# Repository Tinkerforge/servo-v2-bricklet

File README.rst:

Servo Bricklet 2.0
==================

This repository contains the firmware source code and the hardware design
files. The documentation generator configs can be found at
https://github.com/Tinkerforge/generators

Repository Content
------------------

software/:
 * examples/: Examples for all supported languages
 * build/: Compiled files
 * src/: Source code of firmware
 * Makefile: Makefile to build project

hardware/:
 * Contains KiCad project files and additionally schematics as PDF

datasheets/:
 * Contains datasheets for sensors and complex ICs that are used

Hardware
--------

The hardware is designed with the open source EDA Suite KiCad
(http://www.kicad.org). Before you are able to open the files,
you have to install the Tinkerforge kicad-libraries
(https://github.com/Tinkerforge/kicad-libraries). You can either clone
them directly in hardware/ or clone them in a separate folder and
symlink them into hardware/
(ln -s kicad_path/kicad-libraries project_path/hardware). After that you
can open the .pro file in hardware/ with KiCad and from there view and
modify the schematics and the PCB layout.

Software
--------

If you want to do your own Brick/Bricklet firmware development we highly
recommend that you use our build environment setup script and read the
tutorial (https://www.tinkerforge.com/en/doc/Tutorials/Tutorial_Build_Environment/Tutorial.html).

To compile the C code we recommend you to install the newest GNU Arm Embedded
Toolchain (https://launchpad.net/gcc-arm-embedded/+download).
You also need to install bricklib2 (https://github.com/Tinkerforge/bricklib2).

You can either clone it directly in software/src/ or clone it in a
separate folder and symlink it into software/src/
(ln -s bricklib_path/bricklib2 project_path/software/src/). Finally make sure to
have CMake installed (http://www.cmake.org/cmake/resources/software.html).

After that you can build the firmware by invoking make in software/.
The firmware (.zbin) can then be found in software/build/ and uploaded
with brickv (click button "Flashing" on start screen).

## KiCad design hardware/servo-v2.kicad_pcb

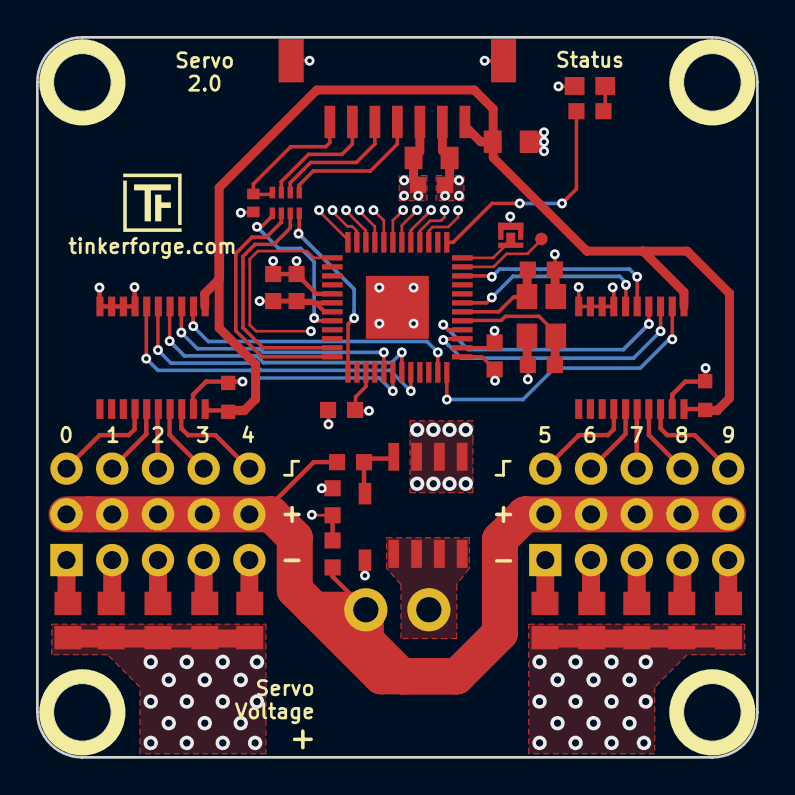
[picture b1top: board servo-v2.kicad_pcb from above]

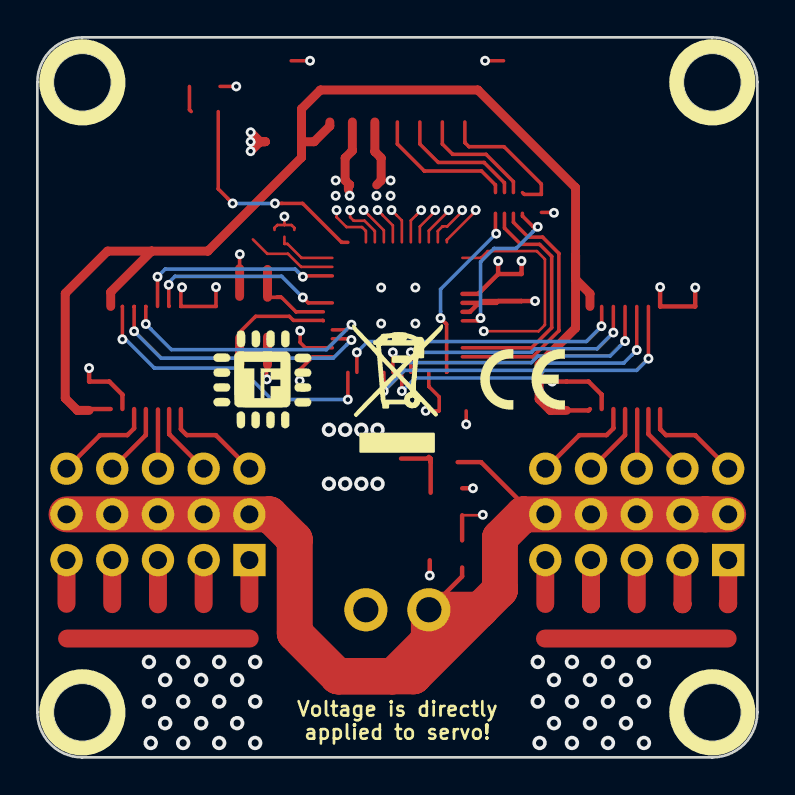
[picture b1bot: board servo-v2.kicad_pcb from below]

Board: 4 copper layers, 40.0 x 40.0 mm, 46 parts (2 on the bottom side), 51 nets.

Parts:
C1, C12: 10uF; C0805
C2: 1uF; C0603F
C3, C4, C5: 100nF; C0603F
C6: 220nF; C0603F
C7: 220pF; C0402F
C8, C9: 10pF; C0603F
C10, C11: 100nF; C0603
D1: Z12V; SOD-123
D3: blue; D0603E
P1: CON-SENSOR2
P2: BOOT; SolderJumper
P3: DEBUG; DEBUG_PAD
P4: black; OQ_2P
Q1: FDS8449; SOIC-8-MOSFET
R1, R3: 1k; R0603F
R2: 10k; R0603F
R4, R5, R6, R7, R8, R9, R10, R11, R12, R13: 0R1; R0805E
R16: 100k; R0603F
RP1: 82; 4X0402
U1: XMC1404; QFN48-EP2
U2, U3, U4, U5: DRILL; DRILL_NP
U6, U7: 74HC245; TSSOP20
U8, U9: Con_Servo_5x; pin_array_5x3
VAL: CE_5mm
VAL#2: WEEE_7mm
X1: 16MHz; CRYSTAL_3225

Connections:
+5V: C10.1, C11.2, C12.1, P1.1, U6.1, U6.20, U7.1, U7.20
CUR-SERVO-0: R8.1, U1.8, U8.A1
CUR-SERVO-1: R7.1, U1.9, U8.B1
CUR-SERVO-2: R6.1, U1.10, U8.C1
CUR-SERVO-3: R5.1, U1.11, U8.D1
CUR-SERVO-4: R4.1, U1.12, U8.E1
CUR-SERVO-5: R13.1, U1.3, U9.A1
CUR-SERVO-6: R12.1, U1.4, U9.B1
CUR-SERVO-7: R11.1, U1.5, U9.C1
CUR-SERVO-8: R10.1, U1.6, U9.D1
CUR-SERVO-9: R9.1, U1.7, U9.E1
GND: C1.1, C2.1, C3.2, C4.2, C5.2, C6.2, C7.2, C8.2, C9.2, C10.2, C11.1, C12.2, D1.1, P1.2, P1.EP, P2.1, Q1.S, R3.2, R4.2, R5.2, R6.2, R7.2, R8.2, R9.2, R10.2, R11.2, R12.2, R13.2, U1.17, U1.37, U1.EP, U6.7, U6.8, U6.9, U6.10, U6.19, U7.7, U7.8, U7.9, U7.10, U7.19, X1.3
unnamed: C7.1, P1.7, RP1.4
unnamed: C8.1, U1.41, X1.2
unnamed: C9.1, U1.42, X1.1
unnamed: D1.2, Q1.G, R16.1
unnamed: D3.2, R1.2
unnamed: P1.4, RP1.1
unnamed: P1.5, RP1.2
unnamed: P1.6, RP1.3
unnamed: P2.2, U1.48
unnamed: P3.1, U1.47
unnamed: P4.1, R2.1, R16.2, U8.A2, U8.B2, U8.C2, U8.D2, U8.E2, U9.A2, U9.B2, U9.C2, U9.D2, U9.E2
unnamed: P4.2, Q1.D
unnamed: R1.1, U1.1
unnamed: U6.14, U8.A3
unnamed: U6.15, U8.B3
unnamed: U6.16, U8.C3
unnamed: U6.17, U8.D3
unnamed: U6.18, U8.E3
unnamed: U7.14, U9.A3
unnamed: U7.15, U9.B3
unnamed: U7.16, U9.C3
unnamed: U7.17, U9.D3
unnamed: U7.18, U9.E3
PWM-SERVO-0: U1.30, U6.6
PWM-SERVO-1: U1.32, U6.5
PWM-SERVO-2: U1.31, U6.4
PWM-SERVO-3: U1.29, U6.3
PWM-SERVO-4: U1.35, U6.2
PWM-SERVO-5: U1.43, U7.6
PWM-SERVO-6: U1.46, U7.5
PWM-SERVO-7: U1.40, U7.4
PWM-SERVO-8: U1.39, U7.3
PWM-SERVO-9: U1.36, U7.2
S-CLK: RP1.7, U1.23
S-CS: RP1.8, U1.25
S-MISO: RP1.5, U1.20
S-MOSI: RP1.6, U1.24
V-EXT: R2.2, R3.1, U1.13
VCC: C1.2, C2.2, C3.1, C4.1, C5.1, C6.1, D3.1, P1.3, U1.18, U1.19, U1.27, U1.38

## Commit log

2019-06-17 initail push
2019-06-18 new schematic
2019-06-18 added symlib table
2019-06-26 pcb design
2019-09-02 final prototype design, drc check, silkscreen added
2019-09-03 ready for prototype
2019-09-06 ordered version
2019-09-19 Add initial test firmware with basic PWM support
2020-01-16 Add and implement API
    Position and period/pulse width configuration works.
    Motion planning is still missing currently.
2020-03-05 Fix Bricklet name in readme
2020-05-04 Enforce 2ms delay between period start if all periods are set at the same time
2020-11-04 Use uint32_t for acc/deceleration and velocity
2020-11-04 new_position bool will be set by motion planning code
2020-11-04 Check more communication parameter
2020-11-04 Remove debug
2020-11-04 Use uint64_t for adc sum and allow averaging configuration per channel
2020-11-04 Add motion planning (velocity, acceleration, deceleration)
2020-11-04 Add tests
2020-11-04 Add support for position-reached callback
2020-11-05 Add current calibration support
2021-01-14 Use uint16_t servo_channel in position-reached callback
    Just as everywhere else.
2021-01-14 Add examples
2021-01-14 java: Add missing import
2021-01-15 rust: Fix compiler warnings
2021-01-18 Add input voltage measurement error calibration
    Currently i don't understand where this error comes from.
    I tested several Servo Bricklets and they all have the
    same measurement error (off by 5000/5400), so we add some
    fixed calibration values for now.
2021-03-15 added step model
2021-05-27 readme: Remove in-development marker
2021-05-27 Fix .step filename
2021-05-27 Update changelog
2021-05-28 add 3d data
2021-05-28 add schematic
2021-05-28 rename
2021-05-28 complete rename
2021-10-25 Update KiCad link
    https://www.kicad.org/blog/2021/10/Avoid-links-to-former-kicad-domain/
2022-04-19 examples: uc: Rename TF_HalContext to TF_HAL.
2022-04-26 uc: Adapt to bindings changes
2022-07-06 Add license files.
2023-01-23 New standart layout. Switched to Kicad 6
2023-01-25 fix symbols
2023-01-25 Data Cleanup
2023-09-26 moved to kicad 7, updated drill_np
2024-11-21 Fix voltage calculation
2024-11-21 Add ref for 2.0.1
2025-10-04 Fix compatibility with new Docker build image (GCC 14.2.1)

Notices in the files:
hardware/servo-v2.kicad_pcb:
Licensed under CERN OHL v.1.1
Copyright (©) 2023, T.Schneidermann
